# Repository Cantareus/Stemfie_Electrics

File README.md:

# Stemfie_Electrics
PCB Design files and Code for STEMFIE Electrics blocks.

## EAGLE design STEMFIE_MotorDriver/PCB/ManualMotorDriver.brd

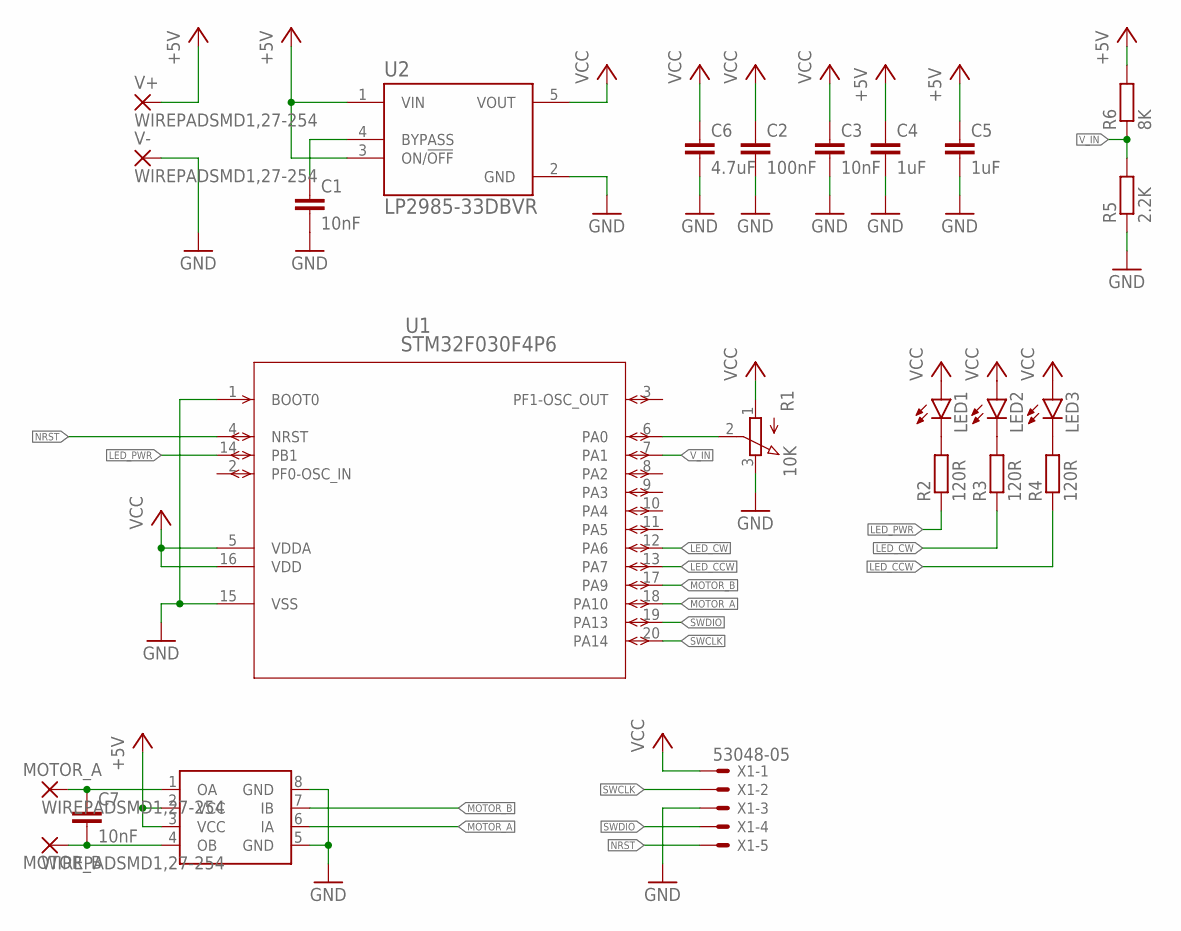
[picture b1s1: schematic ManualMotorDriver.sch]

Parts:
C1, C3: 10nF; C0402K
C2: 100nF; C0402K
C4, C5: 1uF; C0402K
C6: 4.7uF; C0805
C7: 10nF; C0805
LED1, LED2, LED3: LEDCHIP-LED0603; CHIP-LED0603
MOTOR_A: WIREPADSMD1,27-254; SMD1,27-2,54
MOTOR_B: WIREPADSMD1,27-254; SMD1,27-2,54
R1: 10K; EVUFXL
R2, R3, R4: 120R; R0402
R5: 2.2K; R0402
R6: 8K; R0402
U1: STM32F030F4P6; TSSOP20
U2: LP2985-33DBVR; SOT95P280X145-5N
U3: L9110SO8; SO-08
V+: WIREPADSMD1,27-254; SMD1,27-2,54
V-: WIREPADSMD1,27-254; SMD1,27-2,54
X1: 53048-05

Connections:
+5V: C4.1, C5.1, R6.2, U2.1 (VIN), U2.3 (ON/!OFF), U3.2 (VCC), U3.3 (VCC), V+.1
GND: C1.2, C2.2, C3.2, C4.2, C5.2, C6.2, R1.3 (E), R5.1, U1.1 (BOOT0), U1.15 (VSS), U2.2 (GND), U3.5 (GND), U3.8 (GND), V-.1, X1.3
LED_CCW: R4.1, U1.13 (PA7)
LED_CW: R3.1, U1.12 (PA6)
LED_PWR: R2.1, U1.14 (PB1)
MOTOR_A: U1.18 (PA10), U3.6 (IA)
MOTOR_B: U1.17 (PA9), U3.7 (IB)
unnamed: R1.2 (S), U1.6 (PA0)
unnamed: LED1.C, R2.2
unnamed: C1.1, U2.4 (BYPASS)
unnamed: C7.1, MOTOR_A.1, U3.1 (OA)
unnamed: C7.2, MOTOR_B.1, U3.4 (OB)
unnamed: LED2.C, R3.2
unnamed: LED3.C, R4.2
NRST: U1.4 (NRST), X1.5
SWCLK: U1.20 (PA14), X1.2
SWDIO: U1.19 (PA13), X1.4
VCC: C2.1, C3.1, C6.1, LED1.A, LED2.A, LED3.A, R1.1 (A), U1.5 (VDDA), U1.16 (VDD), U2.5 (VOUT), X1.1
V_IN: R5.2, R6.1, U1.7 (PA1)

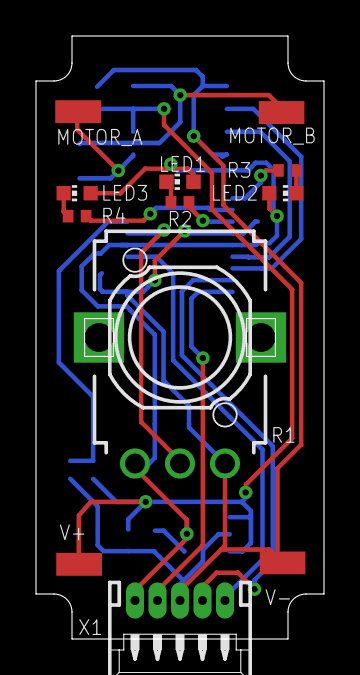
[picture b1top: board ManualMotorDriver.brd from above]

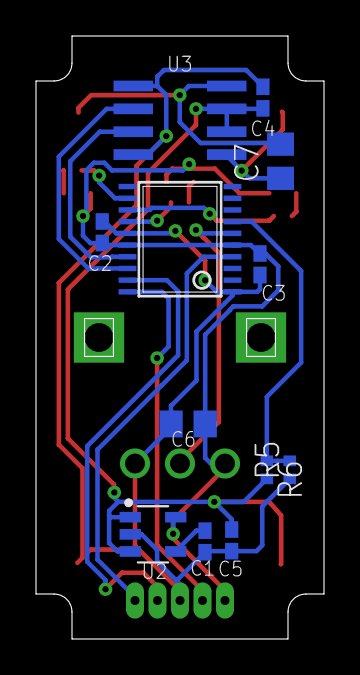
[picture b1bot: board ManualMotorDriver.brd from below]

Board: 2 copper layers, 16.0 x 33.5 mm, 24 parts (12 on the bottom side), 19 nets.

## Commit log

2022-03-11 Create LICENCE
2022-03-11 Add Manual DC Motor Driver PCB
2022-03-11 Fix Potentiometer Center
    Fixed slight potentiometer offset from center.
2022-03-11 Update Library
    Created custom library for parts not in the standard Eagle libraries.
2022-03-11 Fixed NRST
    nRST was pulled down instead of up. Yeah ...
2022-03-13 Added LEDs and reduced size of wire pads

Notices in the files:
parts and their libraries:
COPYRIGHT: Copyright (C) 2022 Ultra Librarian. All rights reserved.
